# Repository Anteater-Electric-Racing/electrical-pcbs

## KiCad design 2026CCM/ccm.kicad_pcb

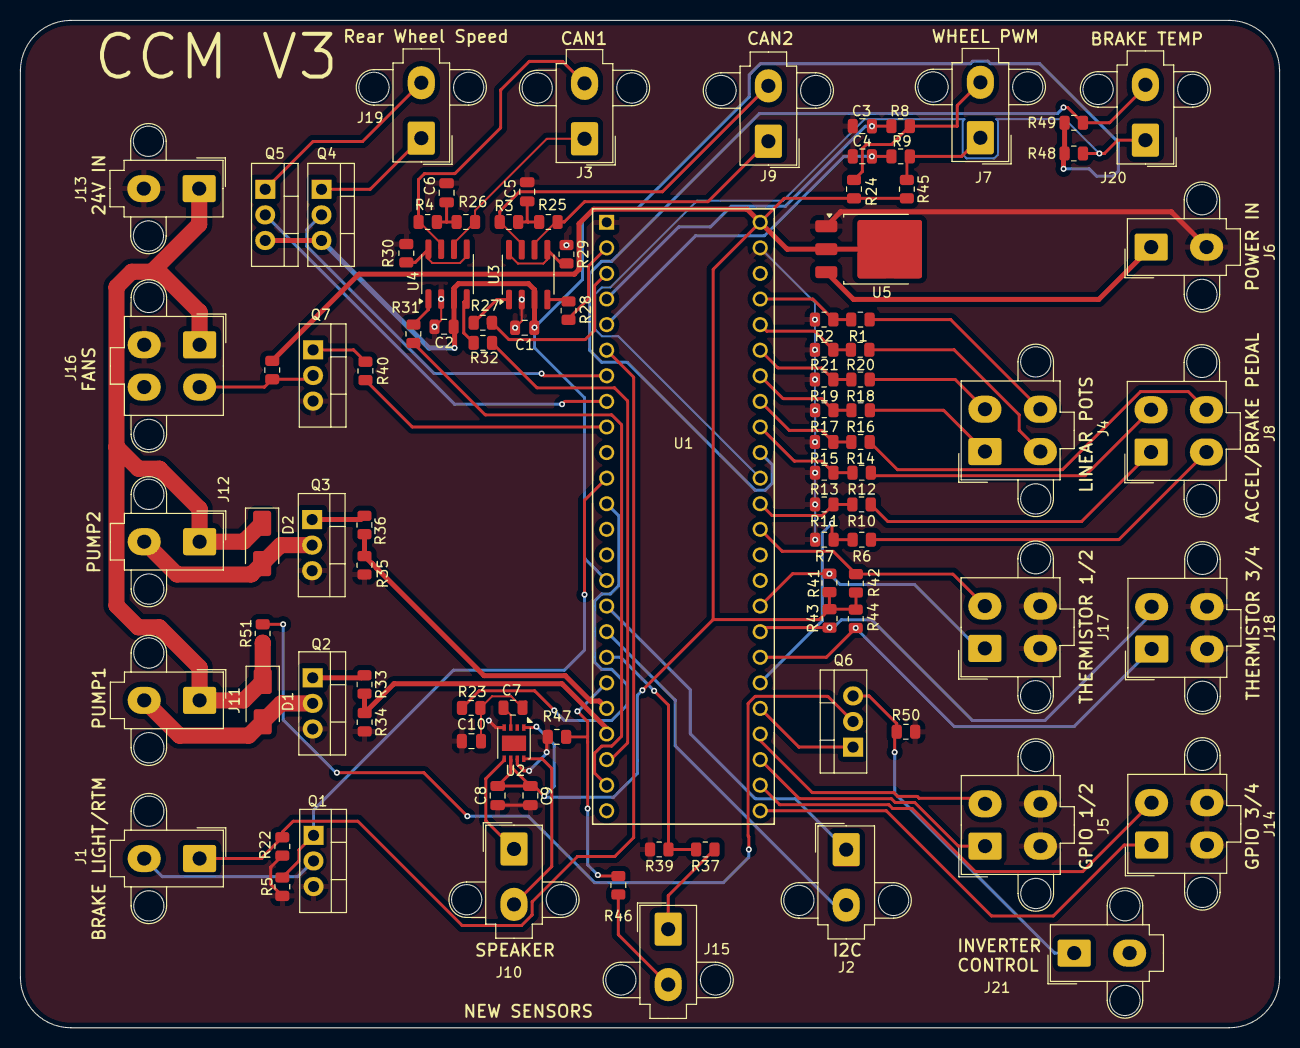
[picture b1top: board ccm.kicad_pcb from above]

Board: 2 copper layers, 125.0 x 100.0 mm, 96 parts (0 on the bottom side), 81 nets.

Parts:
C1, C2, C5, C6: 100 nF; C_0805_2012Metric
C3, C4: 0.01uF; C_0805_2012Metric
C7: 0.1uF; C_0805_2012Metric
C8: 1uF; C_0805_2012Metric
C9: 10uF; C_0805_2012Metric
C10: 10nF; C_0805_2012Metric
D1, D2: SS34; D_SMA
J1, J2, J3, J6, J7, J9, J10, J11, J12, J13, J15, J19, J20, J21: Conn_01x02_Socket; Molex_Mini-Fit_Jr_5566-02A2_2x01_P4.20mm_Vertical
J4, J5, J8, J14, J16, J17, J18: Conn_01x04_Socket; Molex_Mini-Fit_Jr_5566-04A2_2x02_P4.20mm_Vertical
Q1, Q2, Q3, Q4, Q5, Q6, Q7: IRLZ34N; TO-220-3_Vertical
R1, R6, R10, R12, R14, R16, R18, R20: 50k; R_0805_2012Metric
R2, R7, R11, R13, R15, R17, R19, R21: 97k; R_0805_2012Metric
R3, R4, R25, R26, R27, R28, R29, R30, R31, R32: 60; R_0805_2012Metric
R5, R22, R34, R35, R38, R41, R42, R43, R44, R47, R50, R51: 10k; R_0805_2012Metric
R8, R9: 10; R_0805_2012Metric
R23, R40: 1k; R_0805_2012Metric
R24, R45, R48, R49: 4.7k; R_0805_2012Metric
R33, R36: 220; R_0805_2012Metric
R37: 100k; R_0805_2012Metric
R39: 27k; R_0805_2012Metric
R46: 6.5k; R_0805_2012Metric
U1: Teensy4.1; CONN_4848-6000-CP_3MM
U2: PAM8302AAY; DFN-8-1EP_3x3mm_P0.65mm_EP1.55x2.4mm
U3, U4: SN65HVD230; SOIC-8_3.9x4.9mm_P1.27mm
U5: LM1117DT-5.0; TO-252-3_TabPin2

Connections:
+3.3V: C1.1, C2.1, Q4.3 (S), Q5.3 (S), R48.1, R49.1, U1.15 (3V3), U3.3 (VCC), U4.3 (VCC)
+5V: C8.1, C9.1, R24.2, R38.1, R41.2, R42.2, R43.2, R44.2, R45.2, U1.48 (VIN), U2.1 (~SD), U2.6 (VDD), U5.2 (VO)
CANH_1: J9.2, R3.1, U3.7 (CANH)
CANH_2: J3.2, R4.1, U4.7 (CANH)
CANL_1: J9.1, R25.2, U3.6 (CANL)
CANL_2: J3.1, R26.2, U4.6 (CANL)
CAN_RX_1: R28.1, U1.2 (0_RX1_CRX2_CS1)
CAN_RX_2: R32.1, U1.22 (30_CRX3)
CAN_TX_1: R27.1, U1.3 (1_TX1_CTX2_MISO1)
CAN_TX_2: R31.1, U1.23 (31_CTX3)
Fan+: D1.1 (K), D2.1 (K), J11.1, J12.1, J13.1, J16.1, R51.1
Fan_PWM: J16.2, Q7.2 (D), R38.2
GLV-: C1.2, C2.2, C3.2, C4.2, C5.2, C6.2, C8.2, C9.2, C10.1, J5.3, J5.4, J6.2, J13.2, J14.3, J14.4, J16.3, J17.3, J17.4, J18.3, J18.4, Q1.3 (S), Q2.3 (S), Q3.3 (S), Q7.3 (S), R2.2, R5.1, R7.2, R11.2, R13.2, R15.2, R17.2, R19.2, R21.2, R22.1, R29.1, R30.1, R34.2, R35.2, R39.2, R47.2, R50.2, U1.1 (GND), U1.47 (GND), U2.4 (IN-), U2.7 (GND), U3.2 (GND), U4.2 (GND), U5.1 (GND)
unnamed: C5.1, R3.2, R25.1
unnamed: C6.1, R4.2, R26.1
unnamed: C7.2, C10.2, R23.1
unnamed: Q1.1 (G), R5.2, U1.11 (9_OUT1C)
unnamed: Q2.1 (G), R33.1
unnamed: Q3.1 (G), R36.1
unnamed: Q4.2 (D), U1.7 (5_IN2)
unnamed: Q5.2 (D), U1.8 (6_OUT1D)
unnamed: Q6.2 (D), R51.2
unnamed: Q6.1 (G), U1.29 (37_CS)
unnamed: Q7.1 (G), R40.1
unnamed: C3.1, R8.2, U1.4 (2_OUT2)
unnamed: C4.1, R9.2, U1.5 (3_LRCLK2)
unnamed: R40.2, U1.9 (7_RX2_OUT1A)
unnamed: R10.2, R11.1, U1.37 (15_A1_RX3_SPDIF_IN)
unnamed: R12.2, R13.1, U1.40 (18_A4_SDA)
unnamed: R14.2, R15.1, U1.41 (19_A5_SCL)
unnamed: R16.2, R17.1, U1.42 (20_A6_TX5_LRCLK1)
unnamed: R18.2, R19.1, U1.43 (21_A7_RX5_BCLK1)
unnamed: R20.2, R21.1, U1.44 (22_A8_CTX1)
unnamed: R1.2, R2.1, U1.45 (23_A9_CRX1_MCLK1)
unnamed: R37.2, R39.1, U1.18 (26_A12_MOSI1)
unnamed: R46.2, R47.1, U1.19 (27_A13_SCK1)
unnamed: R35.1, R36.2, U1.20 (28_RX7)
unnamed: R33.2, R34.1, U1.21 (29_TX7)
unnamed: R6.2, R7.1, U1.30 (38_CS1_IN1)
unnamed: C7.1, U2.3 (IN+)
unnamed: R27.2, U3.1 (D)
unnamed: R28.2, U3.4 (R)
unnamed: R29.2, U3.5 (Vref), U3.8 (Rs)
unnamed: R31.2, U4.1 (D)
unnamed: R32.2, U4.4 (R)
unnamed: R30.2, U4.5 (Vref), U4.8 (Rs)
PWM_in_1: J7.1, R9.1, R45.1
PWM_in_2: J7.2, R8.1, R24.1
Pump1-: D1.2 (A), J11.2, Q2.2 (D)
Pump2-: D2.2 (A), J12.2, Q3.2 (D)
Vin: J6.1, U5.3 (VI)
acc_ped_1: J8.4, R14.1
acc_ped_2: J8.2, R12.1
brake_1: J8.1, R10.1
brake_2: J8.3, R6.1
brake_light: J1.2, Q1.2 (D)
brake_temp_scl: J20.1, R48.2, U1.38 (16_A2_RX4_SCL1)
brake_temp_sda: J20.2, R49.2, U1.39 (17_A3_TX4_SDA1)
gpio1: J5.2, U1.28 (36_CS)
gpio2: J5.1, U1.27 (35_TX8)
gpio3: J14.2, U1.26 (34_RX8)
gpio4: J14.1, U1.25 (33_MCLK2)
i2c_SCL: J2.1, U1.16 (24_A10_TX6_SCL2)
i2c_SDA: J2.2, U1.17 (25_A11_RX6_SDA2)
kl15: J21.1, Q6.3 (S), R50.1
lin_pot_1: J4.4, R1.1
lin_pot_2: J4.3, R20.1
lin_pot_3: J4.2, R18.1
lin_pot_4: J4.1, R16.1
ready_to_drive_button: J1.1, R22.2, U1.6 (4_BCLK2)
shock_travel: J15.2, R46.1
speaker+: J10.1, U2.5 (OUT+)
speaker-: J10.2, U2.8 (OUT-)
speaker_pwm: R23.2, U1.12 (10_CS_MQSR)
steering_angle: J15.1, R37.1
thermistor1+: J17.2, R41.1, U1.36 (14_A0_TX3_SPDIF_OUT)
thermistor2+: J17.1, R42.1, U1.33 (41_A17)
thermistor3+: J18.2, R43.1, U1.32 (40_A16)
thermistor4+: J18.1, R44.1, U1.31 (39_MISO1_OUT1A)
wheelspeed1: J19.1, Q4.1 (G)
wheelspeed2: J19.2, Q5.1 (G)

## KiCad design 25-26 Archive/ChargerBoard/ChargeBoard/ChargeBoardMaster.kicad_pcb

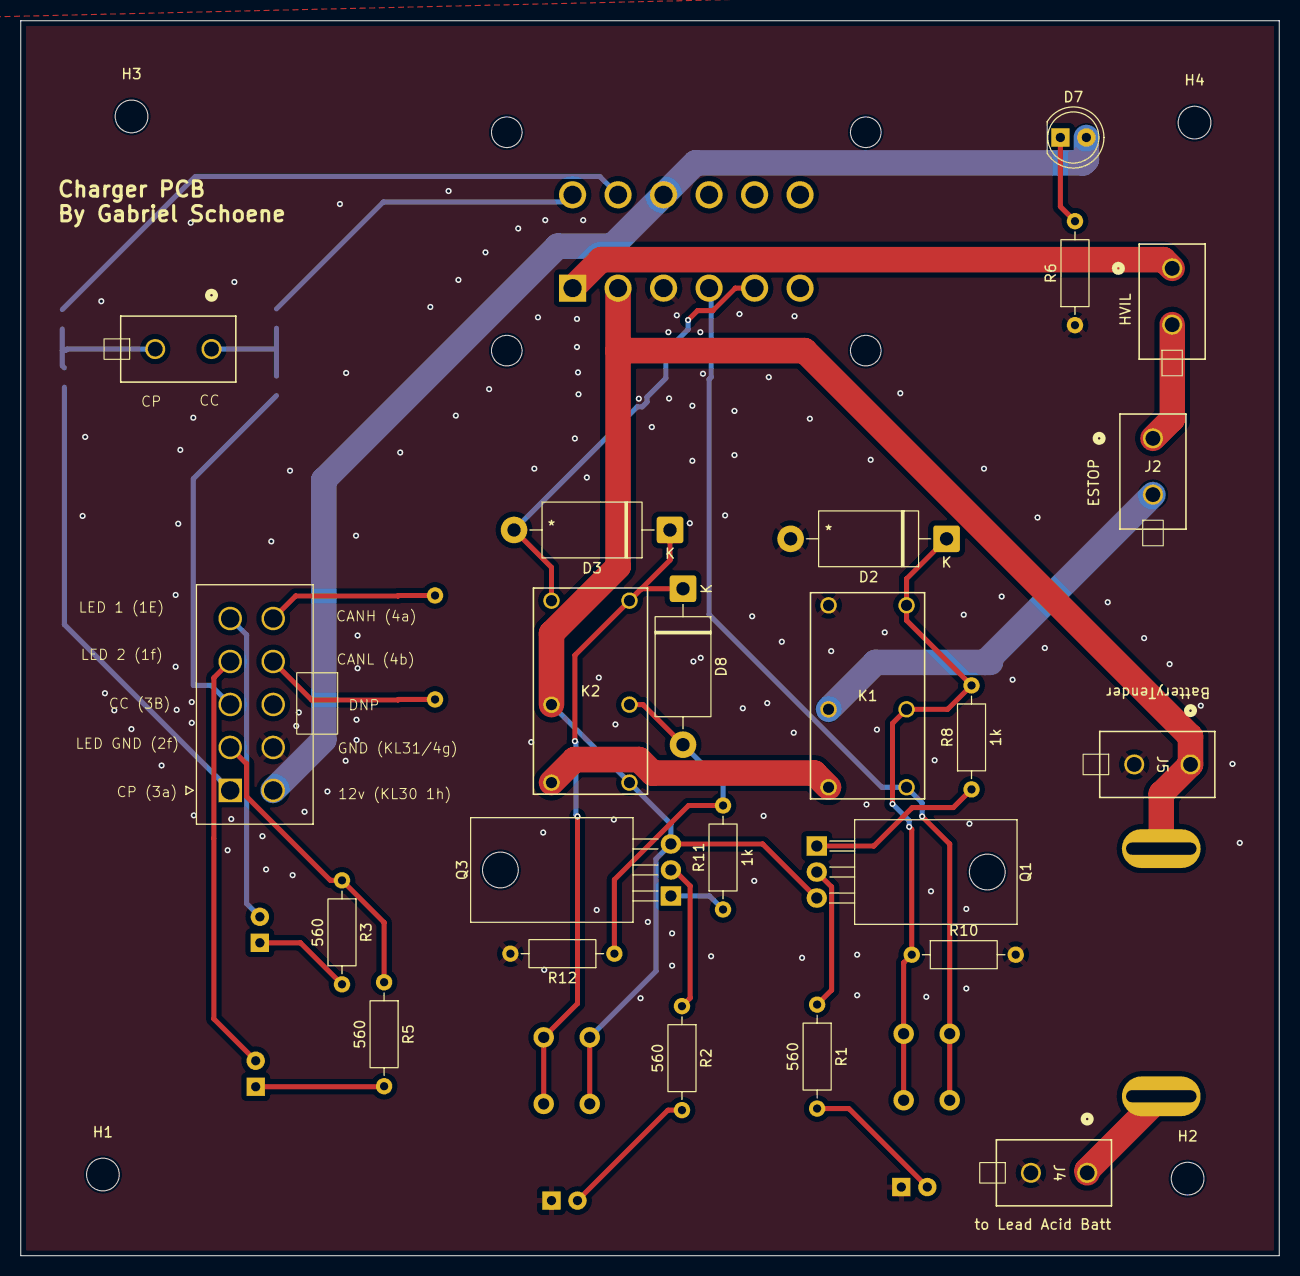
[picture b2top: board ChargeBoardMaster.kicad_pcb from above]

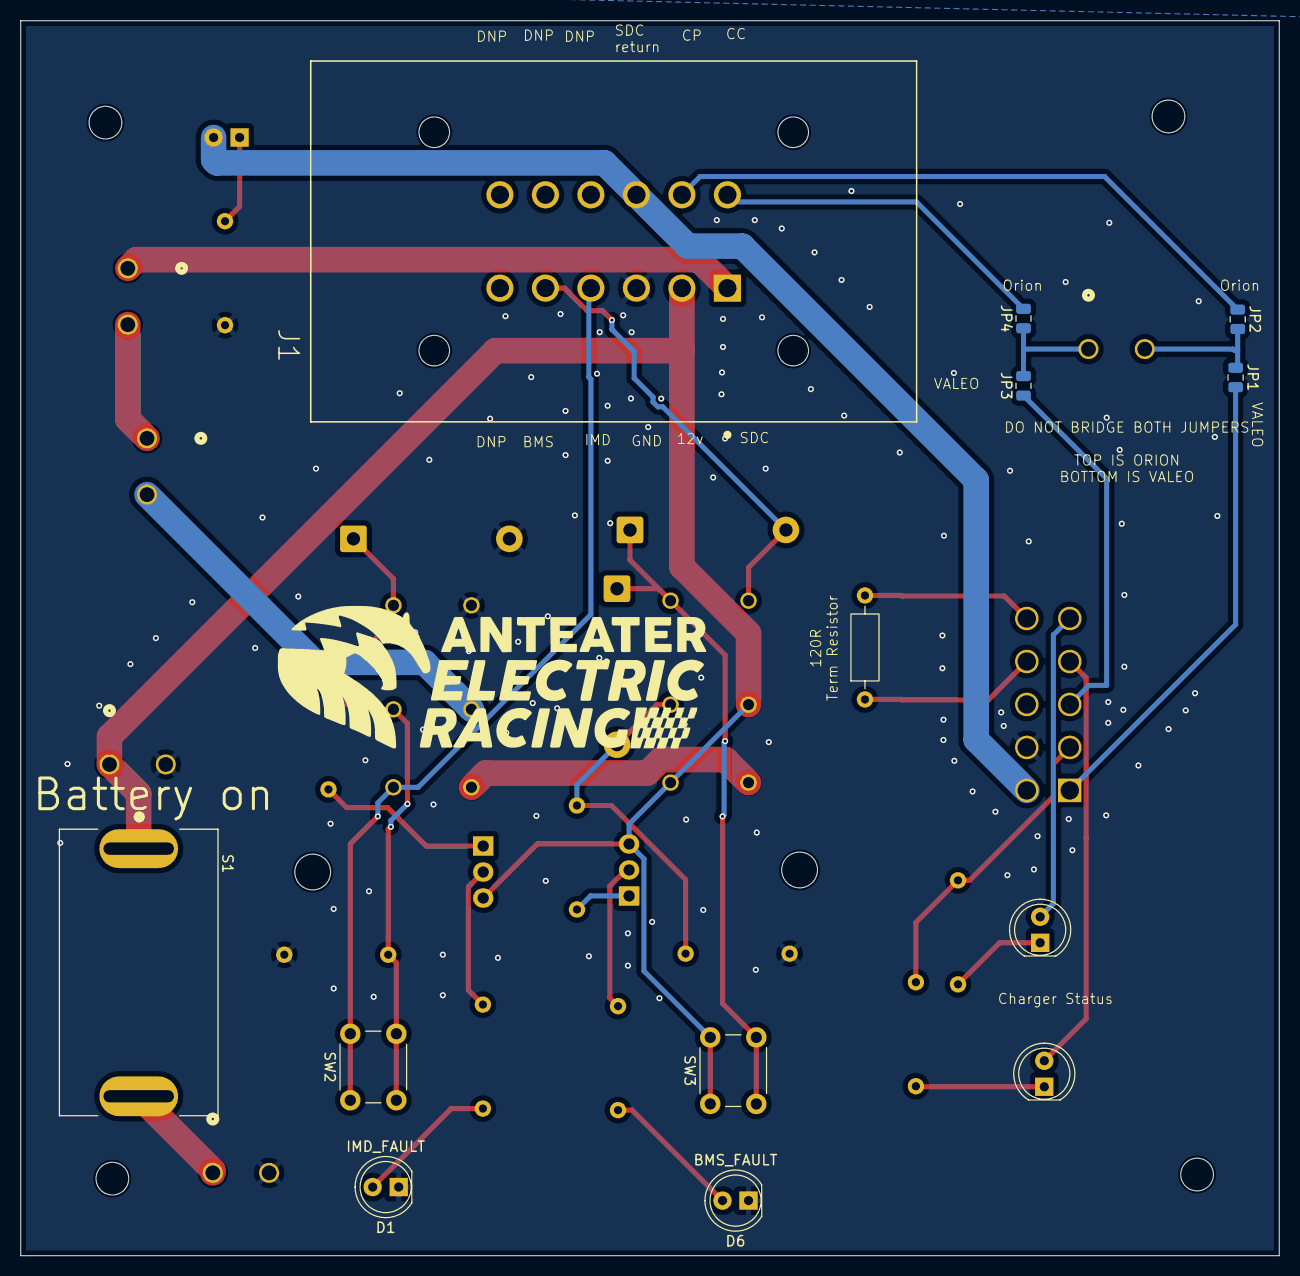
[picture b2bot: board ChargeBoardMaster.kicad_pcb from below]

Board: 2 copper layers, 123.0 x 120.7 mm, 40 parts (13 on the bottom side), 33 nets.

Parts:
D1: IMD_FAULT; LED_D5.0mm
D2, D3, D8: SB560-3G; D_DO-201_P15.24mm_Horizontal
D4, D5, D6: BMS_FAULT; LED_D5.0mm
D7: SDC Return; LED_D5.0mm
H1, H2, H3, H4: MountingHole; MountingHole_3.2mm_M3
J1: DT15-12PA; 12P-DeutschDT
J2: ESTOP; 2pMinifitJR
J3: HVIL; 2pMinifitJR
J4: to Lead Acid Batt; 2pMinifitJR
J5: BatteryTender; 2pMinifitJR
J7: J1772; 2pMinifitJR
J8: 874271042; 10pMinifit
JP1: Valeo CP; C_0805_2012Metric
JP2: Orion CP; C_0805_2012Metric
JP3: Valeo CC; C_0805_2012Metric
JP4: Orion CC; C_0805_2012Metric
K1, K2: G6B-2214P-US DC12; RELAY_G6B-2114P-US_OMR
Q1, Q3: PMOS IRF9540; TO-220-3_Horizontal_TabDown
R1, R2, R3, R5, R6: 560; R_Axial_DIN0207_L6.3mm_D2.5mm_P10.16mm_Horizontal
R8, R11: 1k; R_Axial_DIN0207_L6.3mm_D2.5mm_P10.16mm_Horizontal
R9: 120r; R_Axial_DIN0207_L6.3mm_D2.5mm_P10.16mm_Horizontal
R10, R12: 10k; R_Axial_DIN0207_L6.3mm_D2.5mm_P10.16mm_Horizontal
S1: ST141D00; 20ASwitch
SW2, SW3: SW_Push; SW_PUSH_6mm

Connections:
+12V: J1.2, J5.1, K2.3, K2.5, Q1.3 (S), Q3.3 (S), S1.1, SW3.1
/BMS_FAULT: D3.2 (A), J1.5, K2.1
/CANH: J8.10, R9.2
/CANL: J8.9, R9.1
/CC (orion): J1.12, JP4.2 (B)
/CC (valeo): J8.3, JP3.1 (A)
/CP (orion): J1.11, JP2.1 (A)
/CP (valeo): J8.1, JP1.2 (B)
/IMD_FAULT: J1.4, K1.5, SW2.1
/LED1: D4.2 (A), J8.5
/LED2: D5.2 (A), J8.4
/LED_GND: J8.2, R3.1, R5.1
/Latch/BMSfault_LED: Q3.2 (D), R2.1
/Latch/IMDfault_LED: Q1.2 (D), R1.1
/Latch/bms_reset: D3.1 (K), D8.1 (K), K2.8, SW3.2
/Latch/imd_reset: D2.1 (K), K1.6, K1.8, R8.2, R10.1, SW2.2
/Latch_Out: J2.2, K1.3
/SDC_Out: J1.1, J3.1
/SDC_return: D7.2 (A), J1.10, J8.6
GND: D1.1 (K), D2.2 (A), D6.1 (K), J1.3, J4.2, J5.2, J8.7, K1.1, R6.1, R10.2, R12.2
unnamed: D1.2 (A), R1.2
unnamed: D4.1 (K), R3.2
unnamed: D5.1 (K), R5.2
unnamed: D6.2 (A), R2.2
unnamed: D7.1 (K), R6.2
unnamed: D8.2 (A), K2.6, R11.2, R12.1
unnamed: J2.1, J3.2
unnamed: J4.1, S1.3
unnamed: J7.2, JP1.1 (A), JP2.2 (B)
unnamed: J7.1, JP3.2 (B), JP4.1 (A)
unnamed: K1.4, K2.4
unnamed: Q1.1 (G), R8.1
unnamed: Q3.1 (G), R11.1

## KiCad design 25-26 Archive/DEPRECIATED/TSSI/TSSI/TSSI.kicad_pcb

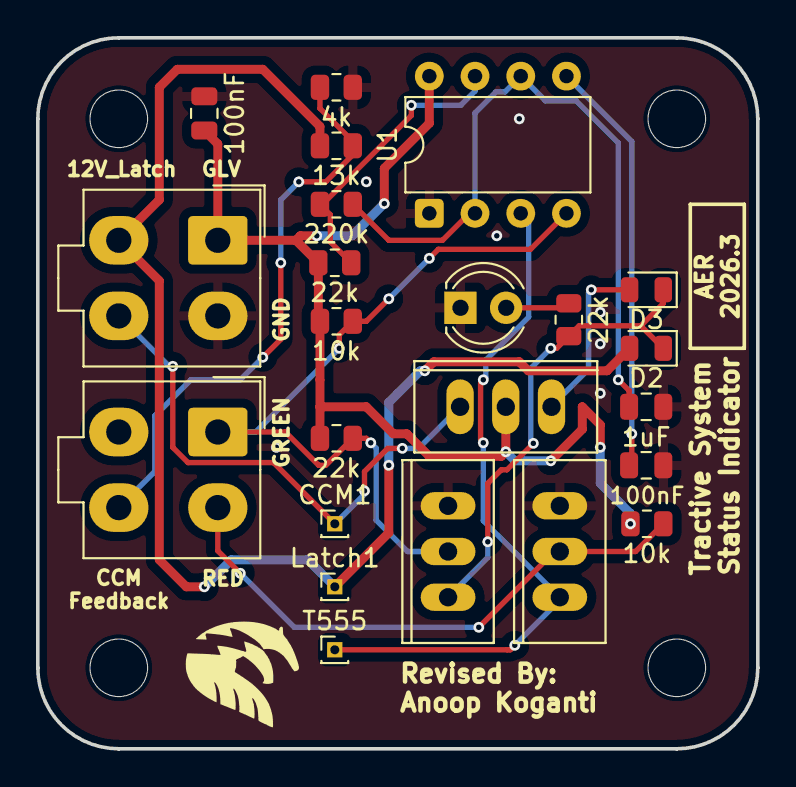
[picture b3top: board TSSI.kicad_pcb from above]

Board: 2 copper layers, 40.0 x 39.5 mm, 27 parts (0 on the bottom side), 14 nets.

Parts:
C1: 1uF; C_0805_2012Metric
C2, C3: 100nF; C_0805_2012Metric
CCM1: TestCCMCtrl; PinHeader_1x01_P1.00mm_Vertical
D1: DEBUGLatch; LED_D4.0mm
D2, D3: RF01VM2S; D_0805_2012Metric
H1, H2, H3, H4: MountingHole; MountingHole_3.2mm_M3
J1, J3: Conn_02x02; Molex_Mini-Fit_Jr_5566-04A2_2x02_P4.20mm_Vertical
Latch1: TestLatch; PinHeader_1x01_P1.00mm_Vertical
Q1, Q3: IRLZ34N; TO-220_2_
R1, R2, R6: 22k; R_0805_2012Metric
R4, R8: 10k; R_0805_2012Metric
R4#2: 13k; R_0805_2012Metric
R5: 4k; R_0805_2012Metric
R7: 220k; R_0805_2012Metric
T555: Test555; PinHeader_1x01_P1.00mm_Vertical
U1: LM555xN; DIP-8_W7.62mm
U3: IRLZ34N; TO-220_2_

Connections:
CCMCTRL: CCM1.1, J1.4, Q1.IN
CCMSensorFeedBack: J3.4, R4#2.2, R5.1
GLV: C3.1, J1.1, Q1.GND, R1.1, R4.1, R6.1, R8.1, U1.8 (VCC)
GND: C1.2, C2.2, C3.2, D1.1 (K), J1.2, Q3.OUT, R5.2, U1.1 (GND), U3.OUT
GREEN_LED: J3.1, Q3.GND, R1.2, R4.2, U1.4 (R)
Latch_12V_Safe: D2.2 (A), J1.3, Latch1.1, R4#2.1
unnamed: D1.2 (A), R2.2
unnamed: D2.1 (K), D3.1 (K), Q3.IN, R2.1
unnamed: D3.2 (A), Q1.OUT
unnamed: T555.1, U1.3 (Q), U3.IN
unnamed: C2.1, U1.5 (CV)
unnamed: R6.2, R7.1, U1.7 (DIS)
unnamed: C1.1, R7.2, U1.2 (TR), U1.6 (THR)
RED_LED: J3.2, R8.2, U3.GND

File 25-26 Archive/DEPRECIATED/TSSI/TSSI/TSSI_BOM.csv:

"Reference","Qty","Value","DNP","Exclude from BOM","Exclude from Board","Footprint","Datasheet","Manufacture Part Number","MANUFACTURER"
"H1,H2,H3,H4","4","MountingHole","","Excluded from BOM","","MountingHole:MountingHole_3.2mm_M3","~","",""
"CCM1","1","TestCCMCtrl","","","","Connector_PinHeader_1.00mm:PinHeader_1x01_P1.00mm_Vertical","https://www.mouser.com/ProductDetail/Molex/39-29-6048?qs=dvx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","39-29-6048 ","Molex"
"J1,J3","2","Conn_02x02","","","","Connector_Molex:Molex_Mini-Fit_Jr_5566-04A2_2x02_P4.20mm_Vertical","https://www.mouser.com/ProductDetail/Molex/39-29-6048?qs=dvx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","39-29-6048 ","Molex"
"Latch1","1","TestLatch","","","","Connector_PinHeader_1.00mm:PinHeader_1x01_P1.00mm_Vertical","https://www.digikey.com/en/products/detail/3m/94980-M000/24773959","94980-M000","3M"
"T555","1","Test555","","","","Connector_PinHeader_1.00mm:PinHeader_1x01_P1.00mm_Vertical","https://www.digikey.com/en/products/detail/3m/94980-M000/24773959","94980-M000","3M"
"C2,C3","2","100nF","","","","Capacitor_SMD:C_0805_2012Metric","https://www.mouser.com/ProductDetail/Murata-Electronics/GCD2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","GCD21BR71H104KA01L","Murata Electronics"
"C1","1","1uF","","","","Capacitor_SMD:C_0805_2012Metric","https://www.digikey.com/en/products/detail/murata-electronic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","GCM21BR7YA105KA55K","Murata Electronics"
"Q1,Q3,U3","3","IRLZ34NPBF","","","","IRLZ34N:TO-220_2_","https://www.digikey.com/en/products/detail/infineon-technolo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","IRLZ34NPBF","Infineon Technologies"
"U1","1","LM555xN","","","","Package_DIP:DIP-8_W7.62mm","http://www.ti.com/lit/ds/symlink/lm555.pdf","LM555CN/NOPB","Texas Instrument"
"R8","1","10k","","","","Resistor_SMD:R_0805_2012Metric","https://www.digikey.com/en/products/detail/yageo/RC0805FR-07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","RC0805FR-0710KL","Yageo"
"R4","1","13k","","","","Resistor_SMD:R_0805_2012Metric","https://www.digikey.com/en/products/detail/yageo/RC0805FR-07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","RC0805FR-0713KL","Yageo"
"R1,R2,R6","3","22k","","","","Resistor_SMD:R_0805_2012Metric","https://www.digikey.com/en/products/detail/yageo/RC0805FR-07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","RC0805FR-0722KL","Yageo"
"R7","1","220k","","","","Resistor_SMD:R_0805_2012Metric","https://www.digikey.com/en/products/detail/yageo/RC0805FR-07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","RC0805FR-07220KL","Yageo"
"R5","1","4k","","","","Resistor_SMD:R_0805_2012Metric","https://www.digikey.com/en/products/detail/yageo/RC0805FR-07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","RC0805FR-0724R9L","Yageo"
"D2,D3","2","SD0805S040S0R5","","","","Diode_SMD:D_0805_2012Metric","https://www.digikey.com/en/products/detail/kyocera-avx/SD080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","SD0805S040S0R5","KYOCERA AVX"
"D1","1","DEBUGLatch","","","","LED_THT:LED_D4.0mm","https://www.digikey.com/en/products/detail/kingbright/WP7113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","WP7113ID","Kingbright"

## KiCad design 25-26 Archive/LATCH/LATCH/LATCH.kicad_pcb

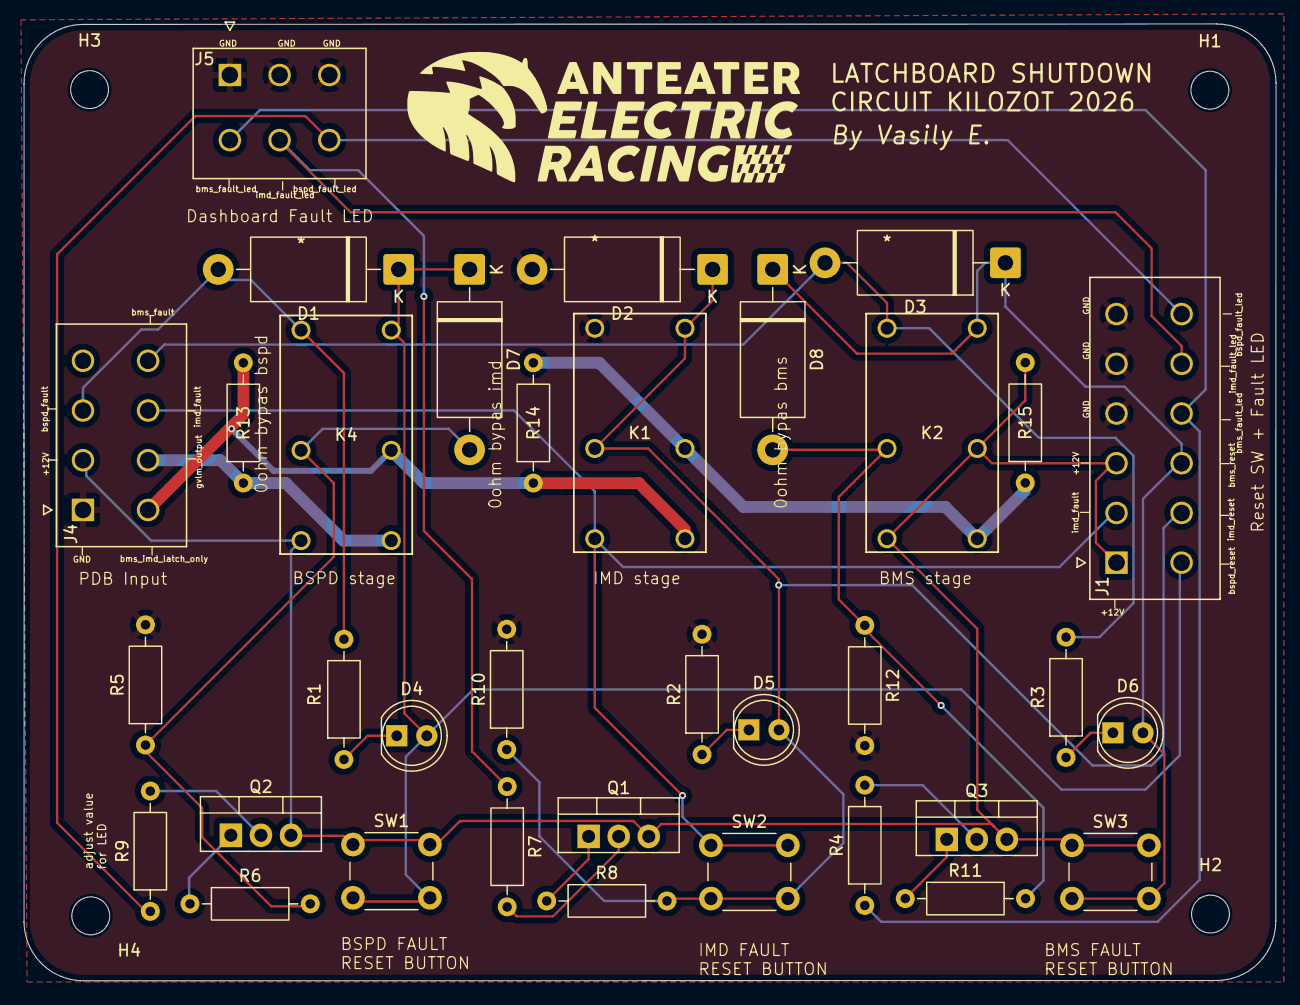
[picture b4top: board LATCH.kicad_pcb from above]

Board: 2 copper layers, 105.8 x 80.8 mm, 39 parts (0 on the bottom side), 25 nets.

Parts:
D1, D2, D3, D7, D8: SB560-3G; D_DO-201_P15.24mm_Horizontal
D4, D5, D6: DEBUG LED; LED_D5.0mm
H1, H2, H3, H4: MountingHole; MountingHole_3.2mm_M3
J1: 39281123; MOLEX_39281123
J4: 39281083; MOLEX_39281083
J5: 39281063; MOLEX_39281063
K1, K2, K4: G6B-2214P-US DC12; RELAY_G6B-2114P-US_OMR
Q1, Q2, Q3: PMOS IRF9540; TO-220-3_Vertical
R1, R2, R3, R6, R8, R11: 1k; R_Axial_DIN0207_L6.3mm_D2.5mm_P10.16mm_Horizontal
R4, R7, R9: 470; R_Axial_DIN0207_L6.3mm_D2.5mm_P10.16mm_Horizontal
R5, R10, R12: 10k; R_Axial_DIN0207_L6.3mm_D2.5mm_P10.16mm_Horizontal
R13, R14, R15: 0; R_Axial_DIN0207_L6.3mm_D2.5mm_P10.16mm_Horizontal
SW1, SW2, SW3: SW_Push; SW_PUSH_6mm

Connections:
+12V: J1.1, J1.3, J4.2, K2.3, K2.5, K4.5, Q1.3 (S), Q2.3 (S), Q3.3 (S), R15.2, SW1.1, SW3.1
BMS_FAULT: D3.2 (A), J4.8, K2.1, R3.2
BMSfault_LED: J1.10, J5.4, R4.1
BSPD_FAULT: D1.2 (A), J4.3, K4.1, R1.2
BSPDfault_LED: J1.12, J5.6, R9.1
GND: D2.2 (A), J1.4, J1.5, J1.6, J4.1, J5.1, J5.2, J5.3, K1.1, R2.2, R5.2, R10.2, R12.2
GVLM_OUTPUT: J4.6, K4.4, R13.1
IMD_FAULT: J1.2, J4.7, K1.5, SW2.1
IMDfault_LED: J1.11, J5.5, R7.1
unnamed: D4.1 (K), R1.1
unnamed: D5.1 (K), R2.1
unnamed: D6.1 (K), R3.1
unnamed: D7.2 (A), K4.6, R5.1, R6.2
unnamed: D8.2 (A), K2.6, R11.2, R12.1
unnamed: K1.3, K2.4, R14.2, R15.1
unnamed: Q1.2 (D), R7.2
unnamed: Q1.1 (G), R8.1
unnamed: Q2.2 (D), R9.2
unnamed: Q2.1 (G), R6.1
unnamed: Q3.2 (D), R4.2
unnamed: Q3.1 (G), R11.1
bms_imd_latch_only: J4.5, K1.4, K4.3, R13.2, R14.1
bms_reset: D3.1 (K), D6.2 (A), D8.1 (K), J1.9, K2.8, SW3.2
bspd_reset: D1.1 (K), D4.2 (A), D7.1 (K), J1.7, K4.8, SW1.2
imd_reset: D2.1 (K), D5.2 (A), J1.8, K1.6, K1.8, R8.2, R10.1, SW2.2

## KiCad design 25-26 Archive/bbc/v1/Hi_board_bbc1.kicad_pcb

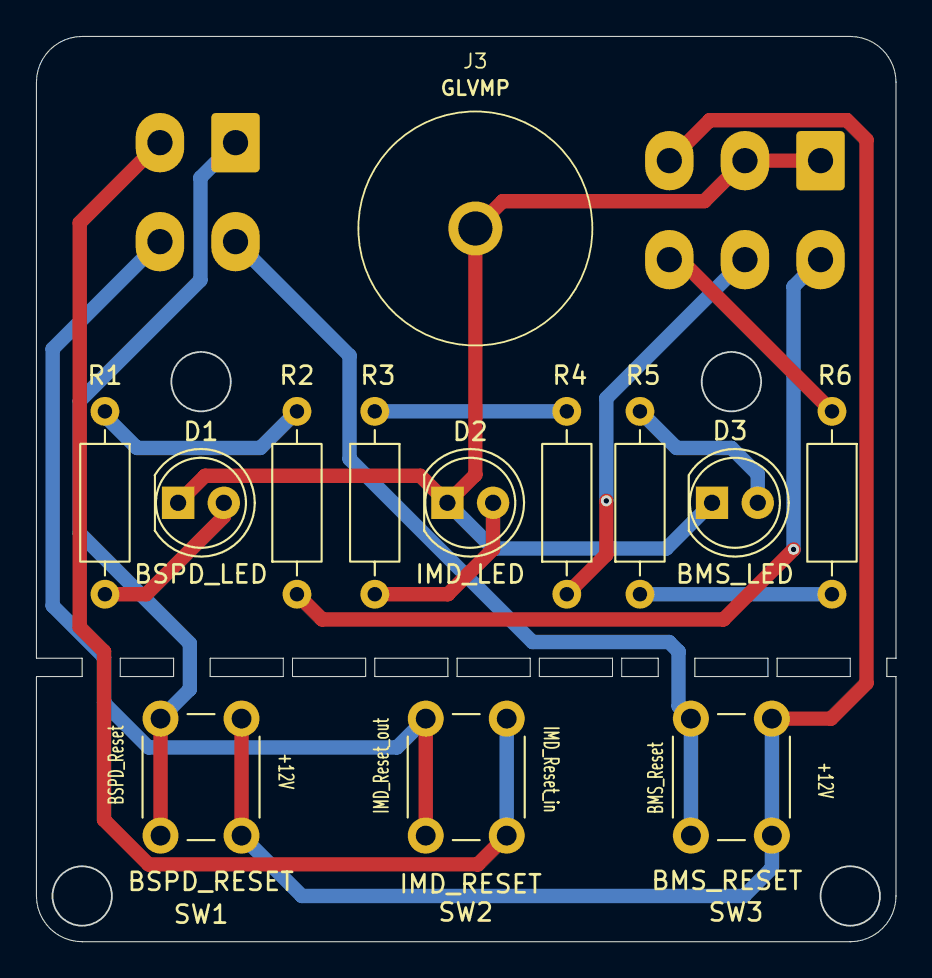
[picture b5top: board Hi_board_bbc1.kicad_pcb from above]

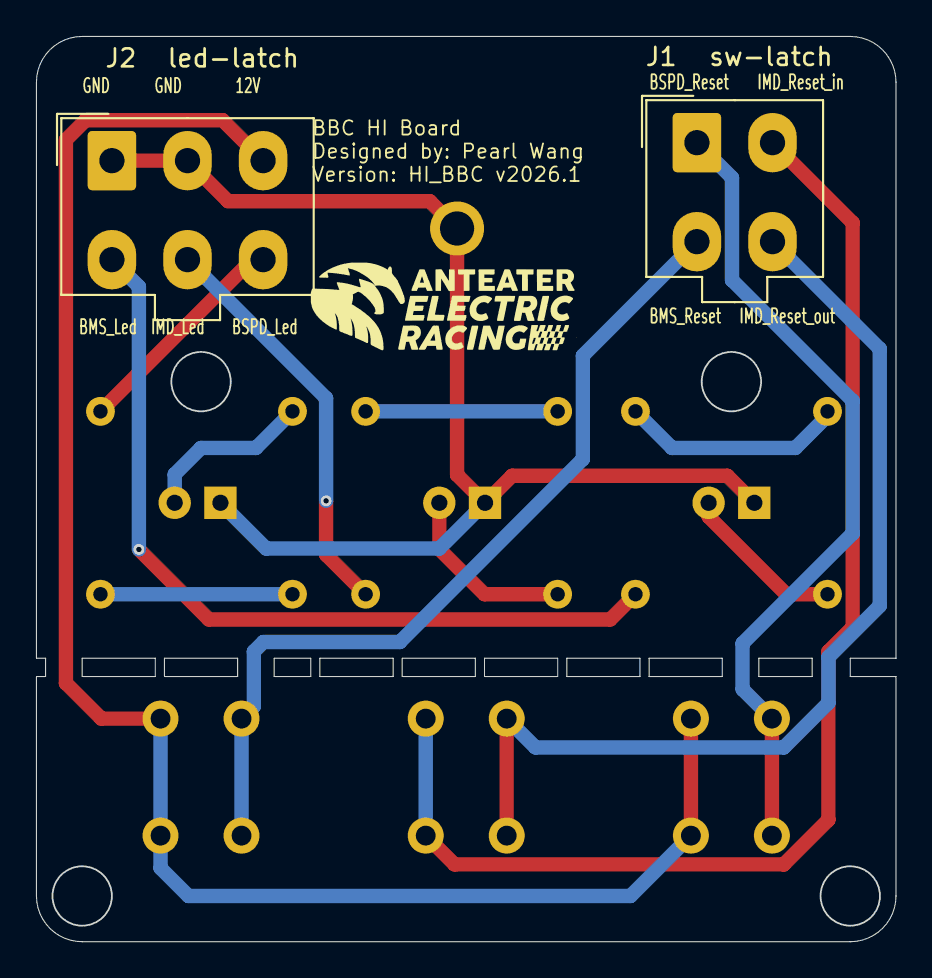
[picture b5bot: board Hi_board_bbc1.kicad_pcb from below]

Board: 2 copper layers, 47.8 x 50.3 mm, 15 parts (2 on the bottom side), 15 nets.

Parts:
D1: BSPD_LED; LED_D5.0mm
D2: IMD_LED; LED_D5.0mm
D3: BMS_LED; LED_D5.0mm
J1: sw-latch; Molex_Mini-Fit_Jr_5566-04A_2x02_P4.20mm_Vertical
J2: led-latch; Molex_Mini-Fit_Jr_5566-06A_2x03_P4.20mm_Vertical
J3: GLVMP; GLVMP_Banana_Jack
R1, R2, R3, R4, R5, R6: 220 ohms; R_Axial_DIN0207_L6.3mm_D2.5mm_P10.16mm_Horizontal
SW1: BSPD_RESET; SW_PUSH_6mm
SW2: IMD_RESET; SW_PUSH_6mm
SW3: BMS_RESET; SW_PUSH_6mm

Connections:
0: D1.1 (K), D2.1 (K), D3.1 (K), J2.1, J2.2, J3.1 (GND)
+12V: J2.3, SW1.2, SW3.2
BMS_LED: J2.6, R6.1
BMS_RESET: J1.3, SW3.1
BSPD_LED: J2.4, R2.1
BSPD_RESET: J1.1, SW1.1
IMD_LED: J2.5, R4.1
IMD_RESET: J1.4, SW2.1
unnamed: D1.2 (A), R1.2
unnamed: D2.2 (A), R3.2
unnamed: D3.2 (A), R5.2
unnamed: J1.2, SW2.2
unnamed: R1.1, R2.2
unnamed: R3.1, R4.2
unnamed: R5.1, R6.2
